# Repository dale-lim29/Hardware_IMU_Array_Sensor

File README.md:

# 16x IMU Sensor Board
This board based on use IMU sensor (ICM42688-P) and Multiplexer (TCA9548A)

## IMU Array Sensor Block Diagram

## IMU Array Sensor Structure

The PCB is designed with a 6-layer stackup:

This multi-layer design ensures proper signal integrity, power distribution, and electromagnetic compatibility for the IMU array sensor system.

### PCB Design Overview

**Complete PCB Layout:**

### PCB Layer Images

**Layer 1:**

**Layer 3:**

**Layer 4:**

**Layer 6:**

## Note

## Firmware Check

To verify the hardware connectivity of the IMU array sensor board, upload the provided firmware to your STM32 microcontroller:

- **Binary file**: `fimware_check/STM32F401.bin`
- **Hex file**: `fimware_check/STM32F401.hex`

Upload either the `.bin` or `.hex` file to your STM32F401 microcontroller to test and validate the hardware connectivity of all IMU sensors in the array. This firmware will help you verify that:
- All IMU sensors are properly connected
- The I2C multiplexer (TCA9548A) is functioning correctly
- Communication with each sensor channel is working as expected

### Expected Output

The expected result shows channel 7 of both multiplexers working correctly with sensors at address 0x68, demonstrating proper hardware connectivity and communication with the IMU array.

## References

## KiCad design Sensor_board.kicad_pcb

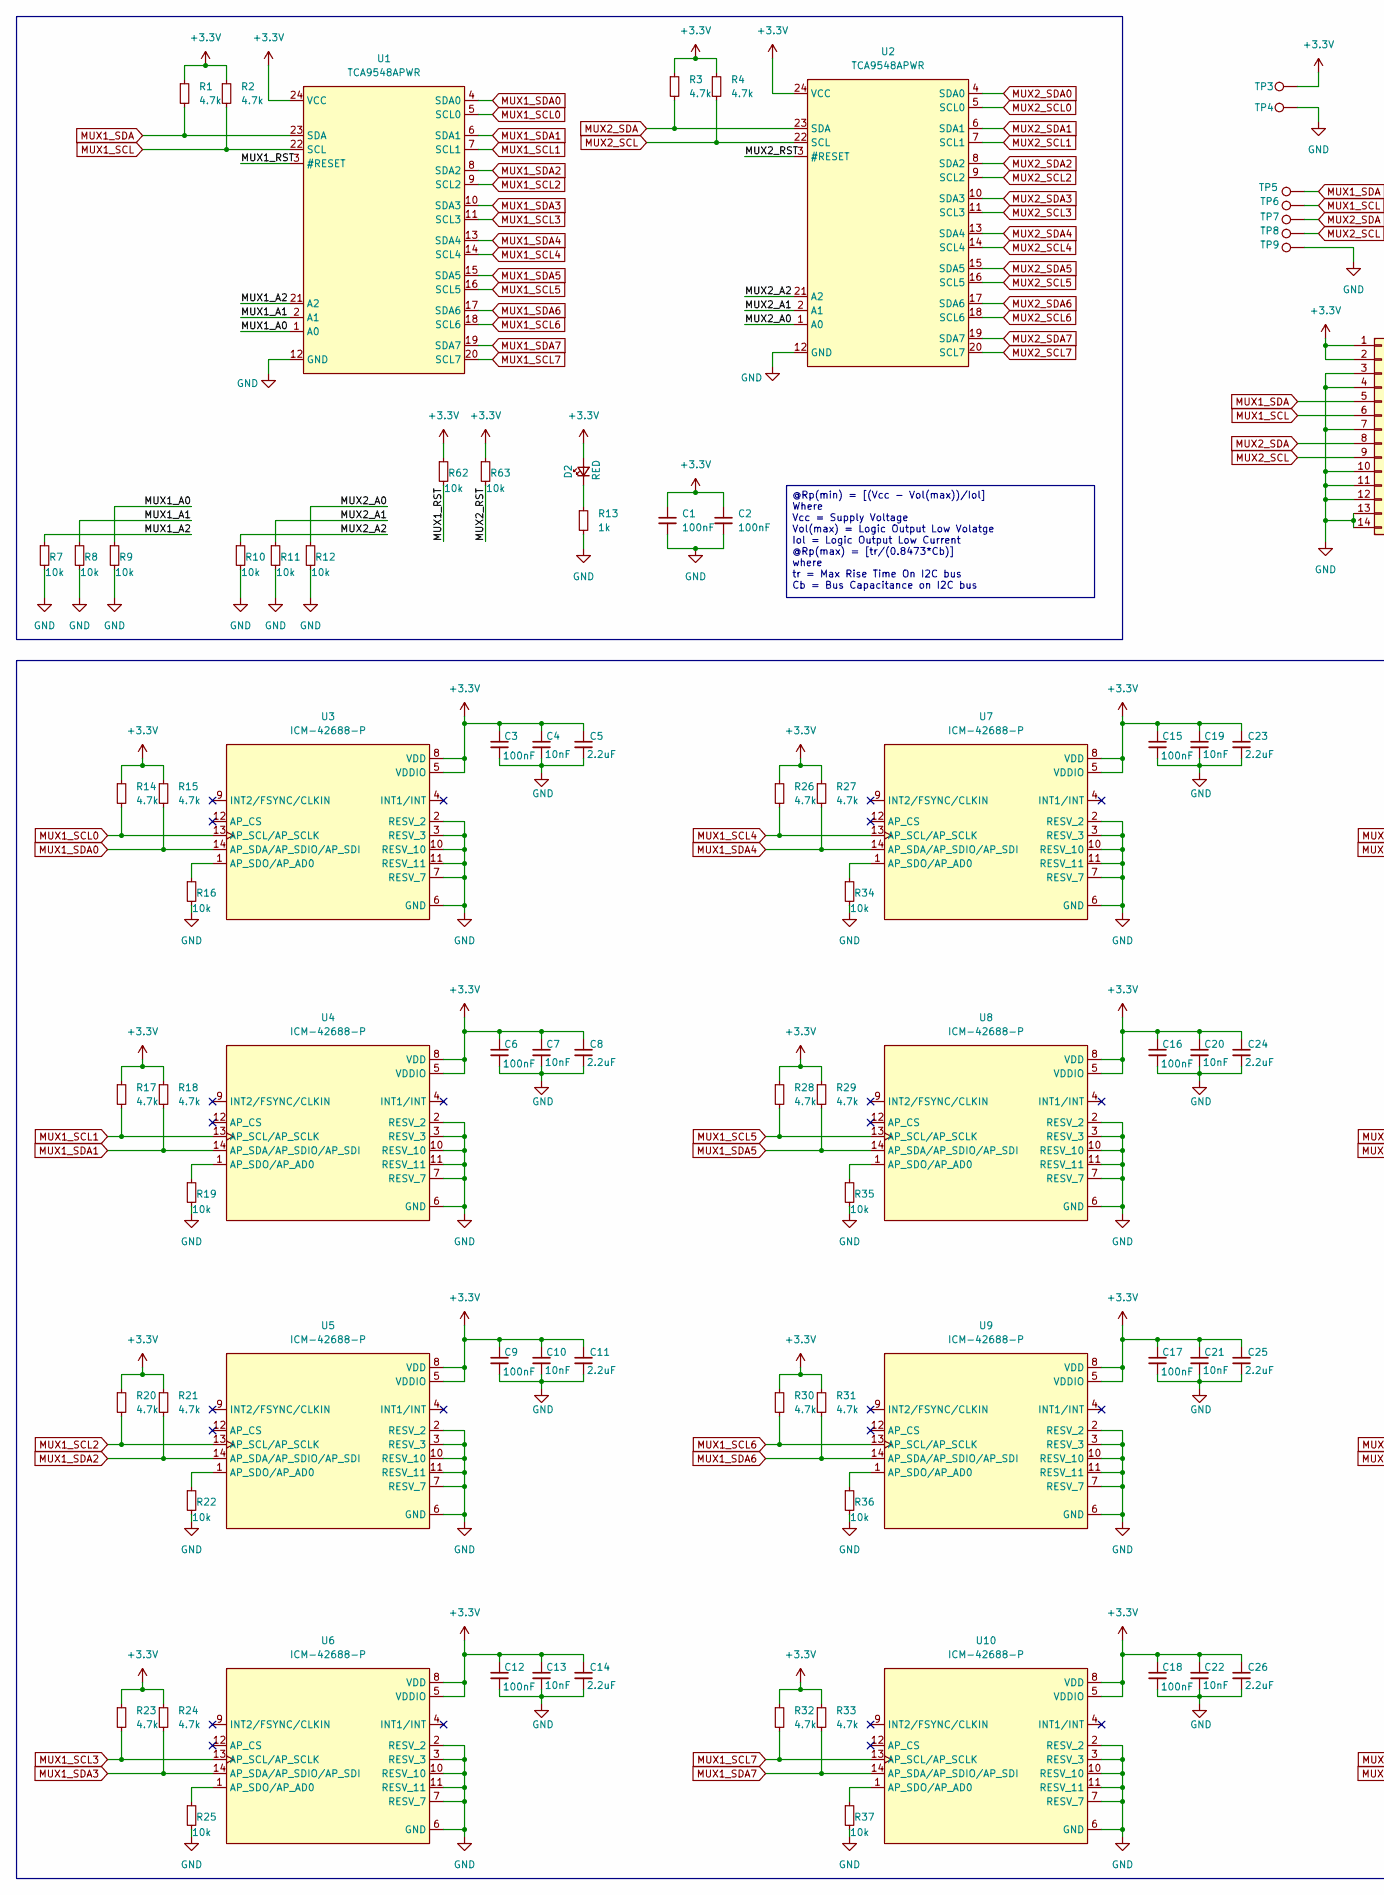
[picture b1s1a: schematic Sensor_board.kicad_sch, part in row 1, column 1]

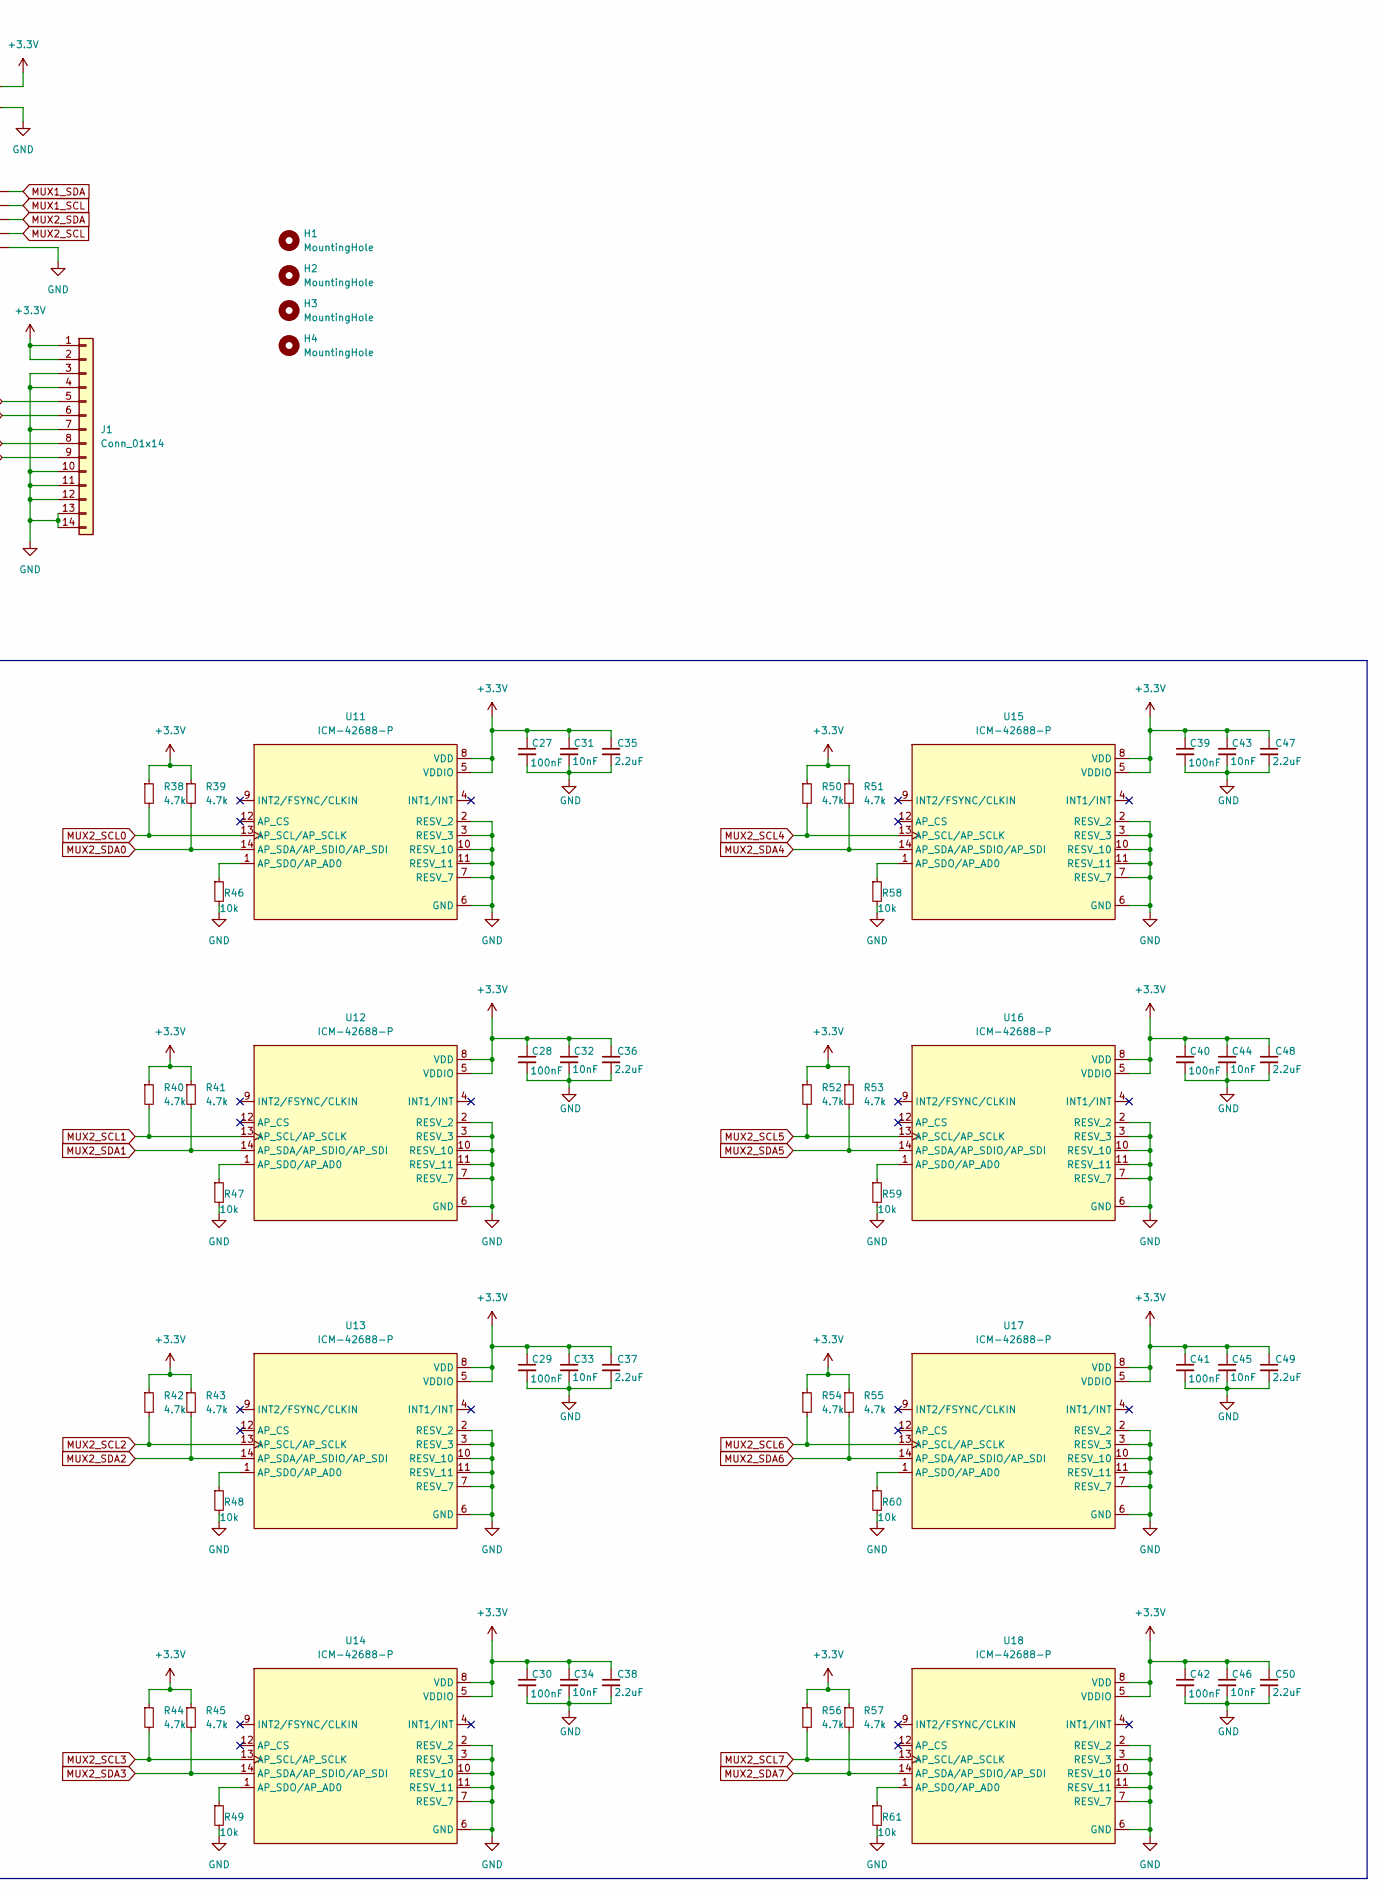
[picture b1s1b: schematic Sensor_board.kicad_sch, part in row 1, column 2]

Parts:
C1, C2, C3, C6, C9, C12, C15, C16, C17, C18, C27, C28, C29, C30, C39, C40, C41, C42: 100nF; C_0603_1608Metric_Pad1.08x0.95mm_HandSolder; Mfr Part # CL10B104KB8NNNC; LCSC Part # C1591
C4, C7, C10, C13, C19, C20, C21, C22, C31, C32, C33, C34, C43, C44, C45, C46: 10nF; C_0603_1608Metric_Pad1.08x0.95mm_HandSolder; Mfr Part # CL10B103KB8NNNC; LCSC Part # C1589
C5, C8, C11, C14, C23, C24, C25, C26, C35, C36, C37, C38, C47, C48, C49, C50: 2.2uF; C_0603_1608Metric_Pad1.08x0.95mm_HandSolder; Mfr Part # CL10A225KO8NNNC; LCSC Part # C23630
D2: RED; LED_0603_1608Metric_Pad1.05x0.95mm_HandSolder; Mfr Part # XL-1608SURC-06; LCSC Part # C965799
H1, H2, H3, H4: MountingHole; MountingHole_2.2mm_M2
J1: Conn_01x14; 1.25-12P WT; Mfr Part # 1.25-12P WT; JLCPCB Part # C5884434
R1, R2, R3, R4, R14, R15, R17, R18, R20, R21, R23, R24, R26, R27, R28, R29, R30, R31, R32, R33, R38, R39, R40, R41, R42, R43, R44, R45, R50, R51, R52, R53, R54, R55, R56, R57: 4.7k; R_0603_1608Metric_Pad0.98x0.95mm_HandSolder; Mfr Part # RC0603FR-074K7L; LCSC Part # C99782
R7, R8, R9, R10, R11, R12, R16, R19, R22, R25, R34, R35, R36, R37, R46, R47, R48, R49, R58, R59, R60, R61, R62, R63: 10k; R_0603_1608Metric_Pad0.98x0.95mm_HandSolder; Mfr Part # RC0402FR-0710KL; LCSC Part # C98220
R13: 1k; R_0603_1608Metric_Pad0.98x0.95mm_HandSolder; Mfr Part # RC0603FR-071KL; LCSC Part # C22548
TP3, TP4, TP5, TP6, TP7, TP8, TP9: TestPoint; TestPoint_Pad_D1.5mm
U1, U2: TCA9548APWR; TSSOP24_1.2mm; Mfr Part # TCA9548APWR; LCSC Part # C130026
U3, U4, U5, U6, U7, U8, U9, U10, U11, U12, U13, U14, U15, U16, U17, U18: ICM-42688-P; PQFN50P300X250X97; Mfr Part # ICM-42688-P; LCSC Part # C1850418

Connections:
+3.3V: C1.1, C2.1, C3.1, C4.1, C5.1, C6.1, C7.1, C8.1, C9.1, C10.1, C11.1, C12.1, C13.1, C14.1, C15.1, C16.1, C17.1, C18.1, C19.1, C20.1, C21.1, C22.1, C23.1, C24.1, C25.1, C26.1, C27.1, C28.1, C29.1, C30.1, C31.1, C32.1, C33.1, C34.1, C35.1, C36.1, C37.1, C38.1, C39.1, C40.1, C41.1, C42.1, C43.1, C44.1, C45.1, C46.1, C47.1, C48.1, C49.1, C50.1, D2.2 (A), J1.1, J1.2, R1.1, R2.1, R3.1, R4.1, R14.1, R15.1, R17.1, R18.1, R20.1, R21.1, R23.1, R24.1, R26.1, R27.1, R28.1, R29.1, R30.1, R31.1, R32.1, R33.1, R38.1, R39.1, R40.1, R41.1, R42.1, R43.1, R44.1, R45.1, R50.1, R51.1, R52.1, R53.1, R54.1, R55.1, R56.1, R57.1, R62.1, R63.1, TP3.1, U1.24 (VCC), U2.24 (VCC), U3.5 (VDDIO), U3.8 (VDD), U4.5 (VDDIO), U4.8 (VDD), U5.5 (VDDIO), U5.8 (VDD), U6.5 (VDDIO), U6.8 (VDD), U7.5 (VDDIO), U7.8 (VDD), U8.5 (VDDIO), U8.8 (VDD), U9.5 (VDDIO), U9.8 (VDD), U10.5 (VDDIO), U10.8 (VDD), U11.5 (VDDIO), U11.8 (VDD), U12.5 (VDDIO), U12.8 (VDD), U13.5 (VDDIO), U13.8 (VDD), U14.5 (VDDIO), U14.8 (VDD), U15.5 (VDDIO), U15.8 (VDD), U16.5 (VDDIO), U16.8 (VDD), U17.5 (VDDIO), U17.8 (VDD), U18.5 (VDDIO), U18.8 (VDD)
/MUX1_A0: R9.1, U1.1 (A0)
/MUX1_A1: R8.1, U1.2 (A1)
/MUX1_A2: R7.1, U1.21 (A2)
/MUX1_RST: R62.2, U1.3 (#RESET)
/MUX2_A0: R12.1, U2.1 (A0)
/MUX2_A1: R11.1, U2.2 (A1)
/MUX2_A2: R10.1, U2.21 (A2)
/MUX2_RST: R63.2, U2.3 (#RESET)
GND: C1.2, C2.2, C3.2, C4.2, C5.2, C6.2, C7.2, C8.2, C9.2, C10.2, C11.2, C12.2, C13.2, C14.2, C15.2, C16.2, C17.2, C18.2, C19.2, C20.2, C21.2, C22.2, C23.2, C24.2, C25.2, C26.2, C27.2, C28.2, C29.2, C30.2, C31.2, C32.2, C33.2, C34.2, C35.2, C36.2, C37.2, C38.2, C39.2, C40.2, C41.2, C42.2, C43.2, C44.2, C45.2, C46.2, C47.2, C48.2, C49.2, C50.2, J1.3, J1.4, J1.7, J1.10, J1.11, J1.12, J1.13, J1.14, R7.2, R8.2, R9.2, R10.2, R11.2, R12.2, R13.2, R16.2, R19.2, R22.2, R25.2, R34.2, R35.2, R36.2, R37.2, R46.2, R47.2, R48.2, R49.2, R58.2, R59.2, R60.2, R61.2, TP4.1, TP9.1, U1.12 (GND), U2.12 (GND), U3.2 (RESV_2), U3.3 (RESV_3), U3.6 (GND), U3.7 (RESV_7), U3.10 (RESV_10), U3.11 (RESV_11), U4.2 (RESV_2), U4.3 (RESV_3), U4.6 (GND), U4.7 (RESV_7), U4.10 (RESV_10), U4.11 (RESV_11), U5.2 (RESV_2), U5.3 (RESV_3), U5.6 (GND), U5.7 (RESV_7), U5.10 (RESV_10), U5.11 (RESV_11), U6.2 (RESV_2), U6.3 (RESV_3), U6.6 (GND), U6.7 (RESV_7), U6.10 (RESV_10), U6.11 (RESV_11), U7.2 (RESV_2), U7.3 (RESV_3), U7.6 (GND), U7.7 (RESV_7), U7.10 (RESV_10), U7.11 (RESV_11), U8.2 (RESV_2), U8.3 (RESV_3), U8.6 (GND), U8.7 (RESV_7), U8.10 (RESV_10), U8.11 (RESV_11), U9.2 (RESV_2), U9.3 (RESV_3), U9.6 (GND), U9.7 (RESV_7), U9.10 (RESV_10), U9.11 (RESV_11), U10.2 (RESV_2), U10.3 (RESV_3), U10.6 (GND), U10.7 (RESV_7), U10.10 (RESV_10), U10.11 (RESV_11), U11.2 (RESV_2), U11.3 (RESV_3), U11.6 (GND), U11.7 (RESV_7), U11.10 (RESV_10), U11.11 (RESV_11), U12.2 (RESV_2), U12.3 (RESV_3), U12.6 (GND), U12.7 (RESV_7), U12.10 (RESV_10), U12.11 (RESV_11), U13.2 (RESV_2), U13.3 (RESV_3), U13.6 (GND), U13.7 (RESV_7), U13.10 (RESV_10), U13.11 (RESV_11), U14.2 (RESV_2), U14.3 (RESV_3), U14.6 (GND), U14.7 (RESV_7), U14.10 (RESV_10), U14.11 (RESV_11), U15.2 (RESV_2), U15.3 (RESV_3), U15.6 (GND), U15.7 (RESV_7), U15.10 (RESV_10), U15.11 (RESV_11), U16.2 (RESV_2), U16.3 (RESV_3), U16.6 (GND), U16.7 (RESV_7), U16.10 (RESV_10), U16.11 (RESV_11), U17.2 (RESV_2), U17.3 (RESV_3), U17.6 (GND), U17.7 (RESV_7), U17.10 (RESV_10), U17.11 (RESV_11), U18.2 (RESV_2), U18.3 (RESV_3), U18.6 (GND), U18.7 (RESV_7), U18.10 (RESV_10), U18.11 (RESV_11)
MUX1_SCL: J1.6, R2.2, TP6.1, U1.22 (SCL)
MUX1_SCL0: R14.2, U1.5 (SCL0), U3.13 (AP_SCL/AP_SCLK)
MUX1_SCL1: R17.2, U1.7 (SCL1), U4.13 (AP_SCL/AP_SCLK)
MUX1_SCL2: R20.2, U1.9 (SCL2), U5.13 (AP_SCL/AP_SCLK)
MUX1_SCL3: R23.2, U1.11 (SCL3), U6.13 (AP_SCL/AP_SCLK)
MUX1_SCL4: R26.2, U1.14 (SCL4), U7.13 (AP_SCL/AP_SCLK)
MUX1_SCL5: R28.2, U1.16 (SCL5), U8.13 (AP_SCL/AP_SCLK)
MUX1_SCL6: R30.2, U1.18 (SCL6), U9.13 (AP_SCL/AP_SCLK)
MUX1_SCL7: R32.2, U1.20 (SCL7), U10.13 (AP_SCL/AP_SCLK)
MUX1_SDA: J1.5, R1.2, TP5.1, U1.23 (SDA)
MUX1_SDA0: R15.2, U1.4 (SDA0), U3.14 (AP_SDA/AP_SDIO/AP_SDI)
MUX1_SDA1: R18.2, U1.6 (SDA1), U4.14 (AP_SDA/AP_SDIO/AP_SDI)
MUX1_SDA2: R21.2, U1.8 (SDA2), U5.14 (AP_SDA/AP_SDIO/AP_SDI)
MUX1_SDA3: R24.2, U1.10 (SDA3), U6.14 (AP_SDA/AP_SDIO/AP_SDI)
MUX1_SDA4: R27.2, U1.13 (SDA4), U7.14 (AP_SDA/AP_SDIO/AP_SDI)
MUX1_SDA5: R29.2, U1.15 (SDA5), U8.14 (AP_SDA/AP_SDIO/AP_SDI)
MUX1_SDA6: R31.2, U1.17 (SDA6), U9.14 (AP_SDA/AP_SDIO/AP_SDI)
MUX1_SDA7: R33.2, U1.19 (SDA7), U10.14 (AP_SDA/AP_SDIO/AP_SDI)
MUX2_SCL: J1.9, R4.2, TP8.1, U2.22 (SCL)
MUX2_SCL0: R38.2, U2.5 (SCL0), U11.13 (AP_SCL/AP_SCLK)
MUX2_SCL1: R40.2, U2.7 (SCL1), U12.13 (AP_SCL/AP_SCLK)
MUX2_SCL2: R42.2, U2.9 (SCL2), U13.13 (AP_SCL/AP_SCLK)
MUX2_SCL3: R44.2, U2.11 (SCL3), U14.13 (AP_SCL/AP_SCLK)
MUX2_SCL4: R50.2, U2.14 (SCL4), U15.13 (AP_SCL/AP_SCLK)
MUX2_SCL5: R52.2, U2.16 (SCL5), U16.13 (AP_SCL/AP_SCLK)
MUX2_SCL6: R54.2, U2.18 (SCL6), U17.13 (AP_SCL/AP_SCLK)
MUX2_SCL7: R56.2, U2.20 (SCL7), U18.13 (AP_SCL/AP_SCLK)
MUX2_SDA: J1.8, R3.2, TP7.1, U2.23 (SDA)
MUX2_SDA0: R39.2, U2.4 (SDA0), U11.14 (AP_SDA/AP_SDIO/AP_SDI)
MUX2_SDA1: R41.2, U2.6 (SDA1), U12.14 (AP_SDA/AP_SDIO/AP_SDI)
MUX2_SDA2: R43.2, U2.8 (SDA2), U13.14 (AP_SDA/AP_SDIO/AP_SDI)
MUX2_SDA3: R45.2, U2.10 (SDA3), U14.14 (AP_SDA/AP_SDIO/AP_SDI)
MUX2_SDA4: R51.2, U2.13 (SDA4), U15.14 (AP_SDA/AP_SDIO/AP_SDI)
MUX2_SDA5: R53.2, U2.15 (SDA5), U16.14 (AP_SDA/AP_SDIO/AP_SDI)
MUX2_SDA6: R55.2, U2.17 (SDA6), U17.14 (AP_SDA/AP_SDIO/AP_SDI)
MUX2_SDA7: R57.2, U2.19 (SDA7), U18.14 (AP_SDA/AP_SDIO/AP_SDI)
unnamed: D2.1 (K), R13.1
unnamed: R16.1, U3.1 (AP_SDO/AP_AD0)
unnamed: R19.1, U4.1 (AP_SDO/AP_AD0)
unnamed: R22.1, U5.1 (AP_SDO/AP_AD0)
unnamed: R25.1, U6.1 (AP_SDO/AP_AD0)
unnamed: R34.1, U7.1 (AP_SDO/AP_AD0)
unnamed: R35.1, U8.1 (AP_SDO/AP_AD0)
unnamed: R36.1, U9.1 (AP_SDO/AP_AD0)
unnamed: R37.1, U10.1 (AP_SDO/AP_AD0)
unnamed: R46.1, U11.1 (AP_SDO/AP_AD0)
unnamed: R47.1, U12.1 (AP_SDO/AP_AD0)
unnamed: R48.1, U13.1 (AP_SDO/AP_AD0)
unnamed: R49.1, U14.1 (AP_SDO/AP_AD0)
unnamed: R58.1, U15.1 (AP_SDO/AP_AD0)
unnamed: R59.1, U16.1 (AP_SDO/AP_AD0)
unnamed: R60.1, U17.1 (AP_SDO/AP_AD0)
unnamed: R61.1, U18.1 (AP_SDO/AP_AD0)

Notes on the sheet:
@Rp(min) = [(Vcc - Vol(max))/Iol] Where Vcc = Supply Voltage Vol(max) = Logic Output Low Volatge Iol = Logic Output Low Current @Rp(max) = [tr/(0.8473*Cb)] where tr = Max Rise Time On I2C bus Cb = Bus Capacitance on I2C bus

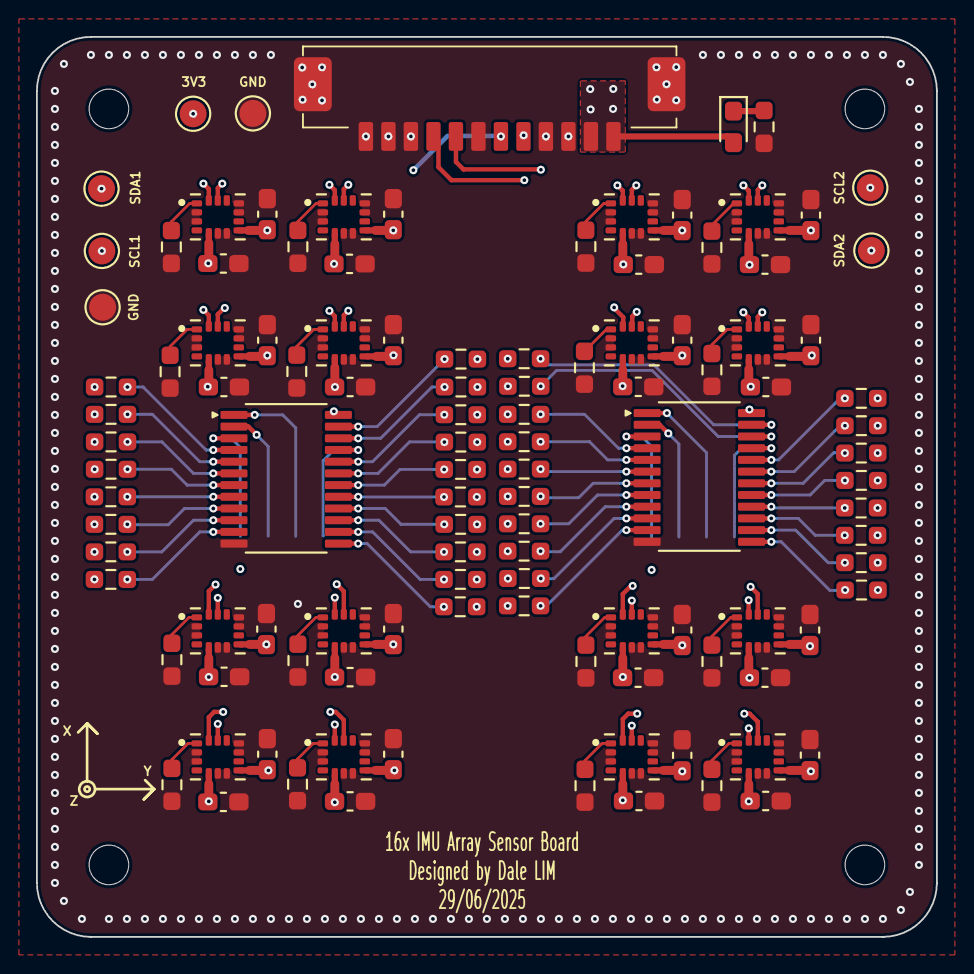
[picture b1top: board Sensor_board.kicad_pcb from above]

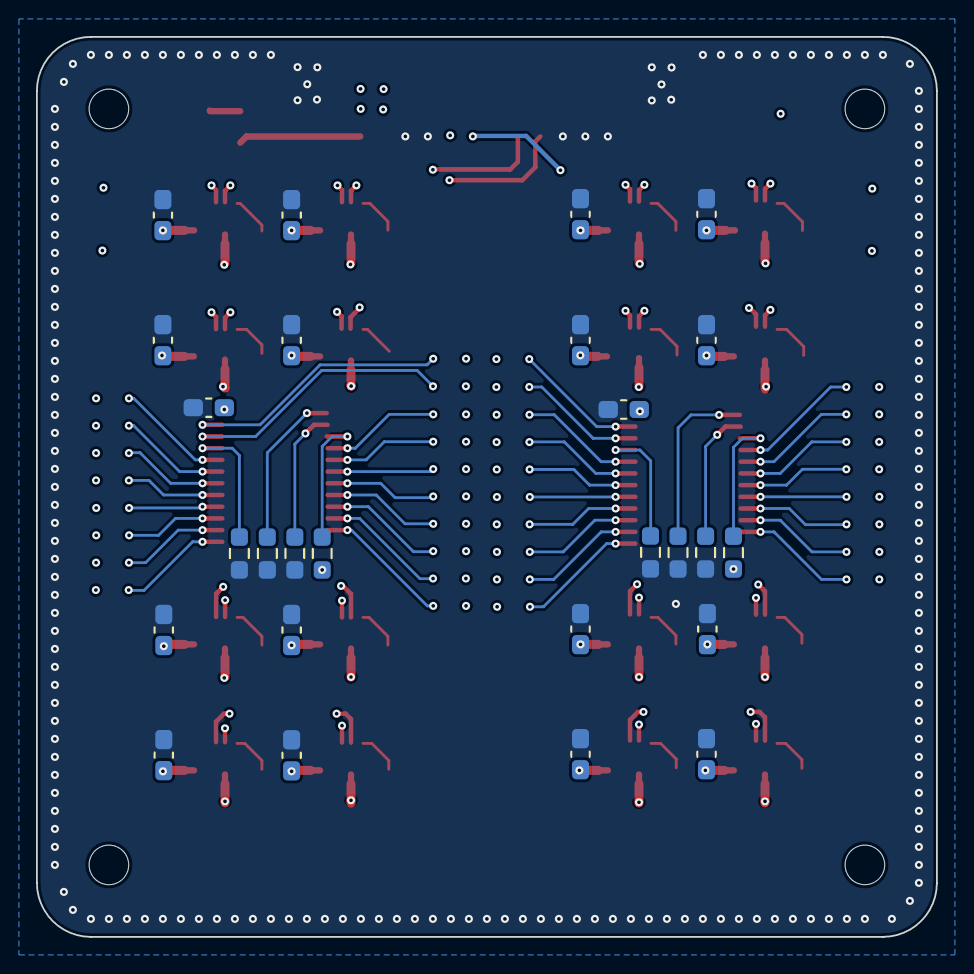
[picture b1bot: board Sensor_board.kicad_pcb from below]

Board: 6 copper layers, 50.0 x 50.0 mm, 142 parts (26 on the bottom side), 63 nets.

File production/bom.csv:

Designator,Footprint,Quantity,Value,LCSC Part #
"C1, C12, C15, C16, C17, C18, C2, C27, C28, C29, C3, C30, C39, C40, C41, C42, C6, C9",0603,18,100nF,C1591
"C10, C13, C19, C20, C21, C22, C31, C32, C33, C34, C4, C43, C44, C45, C46, C7",0603,16,10nF,C1589
"C11, C14, C23, C24, C25, C26, C35, C36, C37, C38, C47, C48, C49, C5, C50, C8",0603,16,2.2uF,C23630
D2,0603,1,RED,C965799
"H1, H2, H3, H4",MountingHole_2.2mm_M2,4,MountingHole,
J1,1.25-12P WT,1,Conn_01x14,
"R1, R14, R15, R17, R18, R2, R20, R21, R23, R24, R26, R27, R28, R29, R3, R30, R31, R32, R33, R38, R39, R4, R40, R41, R42, R43, R44, R45, R50, R51, R52, R53, R54, R55, R56, R57",0603,36,4.7k,C99782
"R10, R11, R12, R16, R19, R22, R25, R34, R35, R36, R37, R46, R47, R48, R49, R58, R59, R60, R61, R62, R63, R7, R8, R9",0603,24,10k,C98220
R13,0603,1,1k,C22548
"TP3, TP4, TP5, TP6, TP7, TP8, TP9",TestPoint_Pad_D1.5mm,7,TestPoint,
"U1, U2",TSSOP24_1.2mm,2,TCA9548APWR,C130026
"U10, U11, U12, U13, U14, U15, U16, U17, U18, U3, U4, U5, U6, U7, U8, U9",PQFN50P300X250X97,16,ICM-42688-P,C1850418

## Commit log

2025-08-02 update readme based layout
2025-08-03 add sensor block diagram
